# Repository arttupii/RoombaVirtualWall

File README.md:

Roomba iRobot virtualwall

 - For Roomba 500, 600, 700, 800 and 900 series
 - Uses two AA battery (2x1.5V=3V)
 - ATTINY85 Microcontroller

```
     <----------490us and 19 pulses----------------->
     <---25us---->                                   <--- 130ms (power down      ) ---->
     
     |-----|     |-----|          |-----|     |-----|                                   |------|
     |     |     |     |          |     |     |     |                                   |      |
     |     |     |     |          |     |     |     |                                   |      |
     |     |     |     |          |     |     |     |                                   |      |
_____|     |_____|     |_____.....|     |_____|     |_______________......______________|      |____
```

R1=47R

R2=200R

VCC=2x1.5V(AA battery) = 3V

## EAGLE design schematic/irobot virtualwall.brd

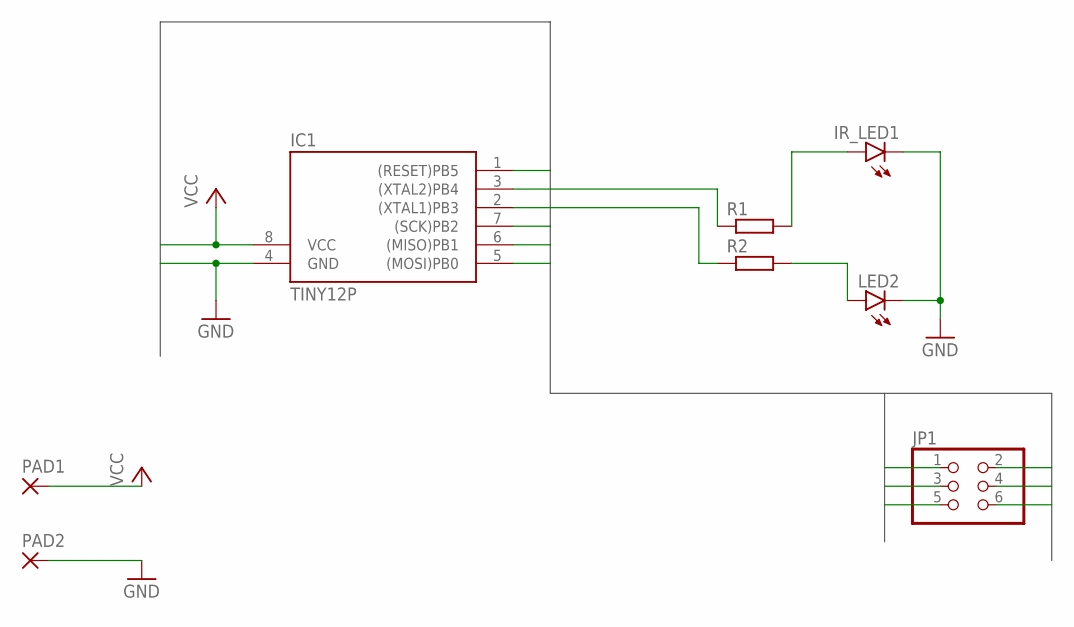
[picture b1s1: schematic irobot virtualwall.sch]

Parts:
IC1: TINY12P; DIL08
IR_LED1: LED5MM
JP1: PINHD-2X3; 2X03
LED2: LED5MM
PAD1, PAD2: 2,54/0,8
R1, R2: R-EU_0207/10; 0207/10

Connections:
CLK: IC1.7 ((SCK)PB2), JP1.3
GND: IC1.4 (GND), IR_LED1.K (C), JP1.6, LED2.K (C), PAD2.1
MISO: IC1.6 ((MISO)PB1), JP1.1
MOSI: IC1.5 ((MOSI)PB0), JP1.4
unnamed: IC1.3 ((XTAL2)PB4), R1.1
unnamed: IC1.2 ((XTAL1)PB3), R2.1
unnamed: IR_LED1.A, R1.2
unnamed: LED2.A, R2.2
RST: IC1.1 ((RESET)PB5), JP1.5
VCC: IC1.8 (VCC), JP1.2, PAD1.1

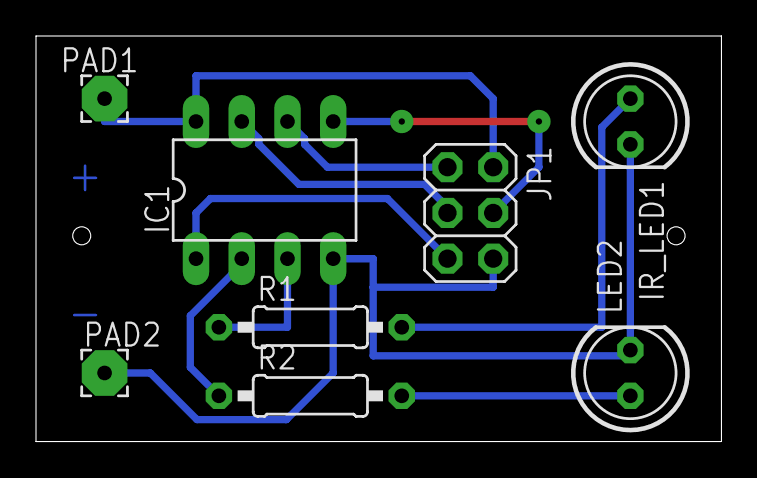
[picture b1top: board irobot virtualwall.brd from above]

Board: 2 copper layers, 38.1 x 22.5 mm, 8 parts (0 on the bottom side), 10 nets.

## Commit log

2020-08-16 Add codes
2020-09-04 Fixed io pins
